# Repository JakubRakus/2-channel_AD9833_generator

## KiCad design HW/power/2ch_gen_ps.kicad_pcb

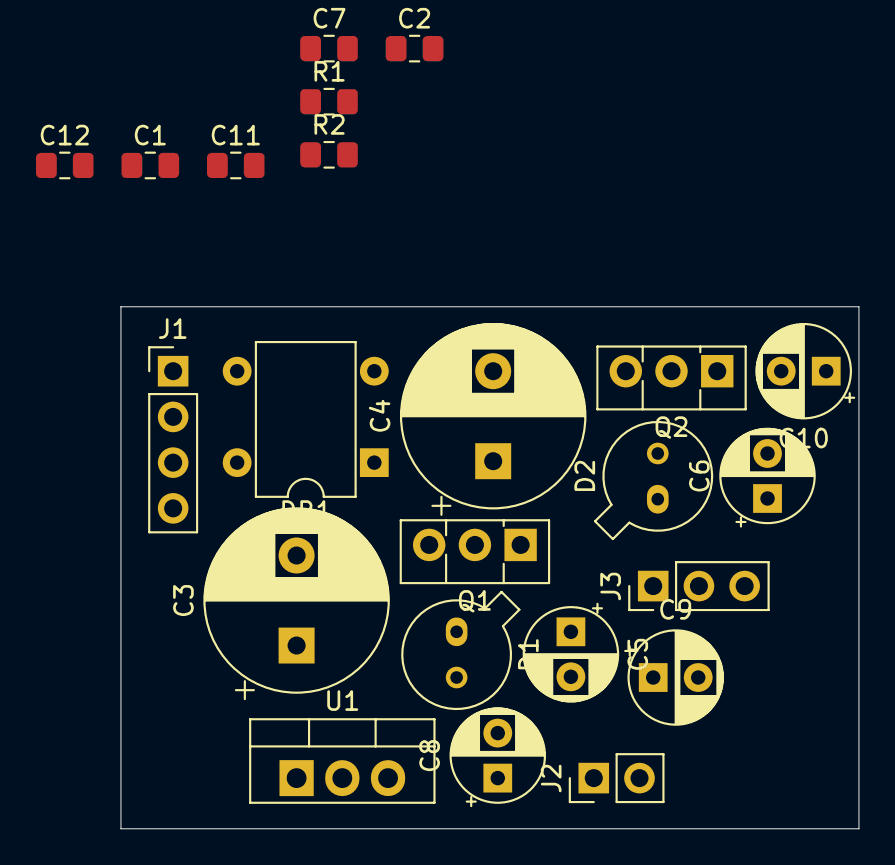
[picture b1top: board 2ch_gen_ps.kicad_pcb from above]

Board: 2 copper layers, 41.0 x 29.0 mm, 23 parts (0 on the bottom side), 10 nets, no tracks yet.

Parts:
C1, C2, C7, C11, C12: 100n; C_0805_2012Metric_Pad1.15x1.40mm_HandSolder
C3, C4: 2200u/16V; CP_Radial_D10.0mm_P5.00mm
C5, C6: 10u; CP_Radial_D5.0mm_P2.50mm
C8: 220u/6.3V; CP_Radial_D5.0mm_P2.50mm
C9, C10: 100u/10V; CP_Radial_D5.0mm_P2.50mm
D1, D2: 6V8; TO-18-2
DB1: DB106; Diode_Bridge_DIP-4_W7.62mm_P5.08mm
J1: Conn_01x04; PinHeader_1x04_P2.54mm_Vertical
J2: Conn_01x02; PinHeader_1x02_P2.54mm_Vertical
J3: Conn_01x03; PinHeader_1x03_P2.54mm_Vertical
Q1: BD139; TO-126-3_Vertical
Q2: BD140; TO-126-3_Vertical
R1, R2: 100R; R_0805_2012Metric_Pad1.15x1.40mm_HandSolder
U1: 7805; TO-220-3_Vertical

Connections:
+5V: C7.1, C8.1, J2.1, U1.3
/AC1: DB1.4, J1.4
/AC2*: DB1.3, J1.1
GND: C1.2, C2.1, C3.2, C4.1, C5.2, C6.1, C7.2, C8.2, C9.2, C10.1, C11.2, C12.1, D1.2, D2.1, J1.2, J1.3, J2.2, J3.2, U1.2
unnamed: C1.1, C3.1, DB1.1, Q1.2, R1.1, U1.1
unnamed: C2.2, C4.2, DB1.2, Q2.2, R2.2
unnamed: C5.1, D1.1, Q1.3, R1.2
unnamed: C6.2, D2.2, Q2.3, R2.1
VDDA: C9.1, C11.1, J3.1, Q1.1
VSSA: C10.2, C12.2, J3.3, Q2.1

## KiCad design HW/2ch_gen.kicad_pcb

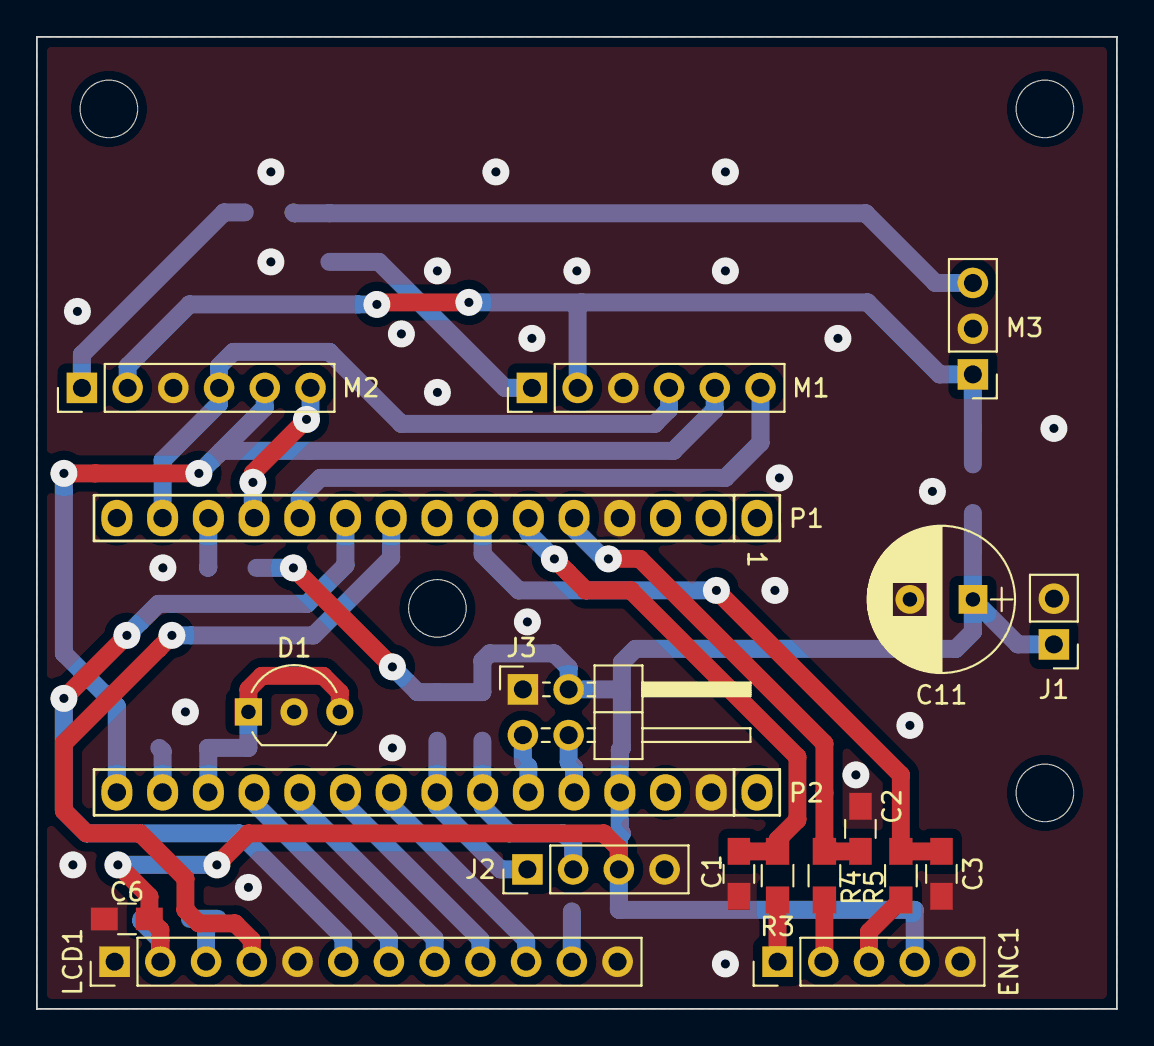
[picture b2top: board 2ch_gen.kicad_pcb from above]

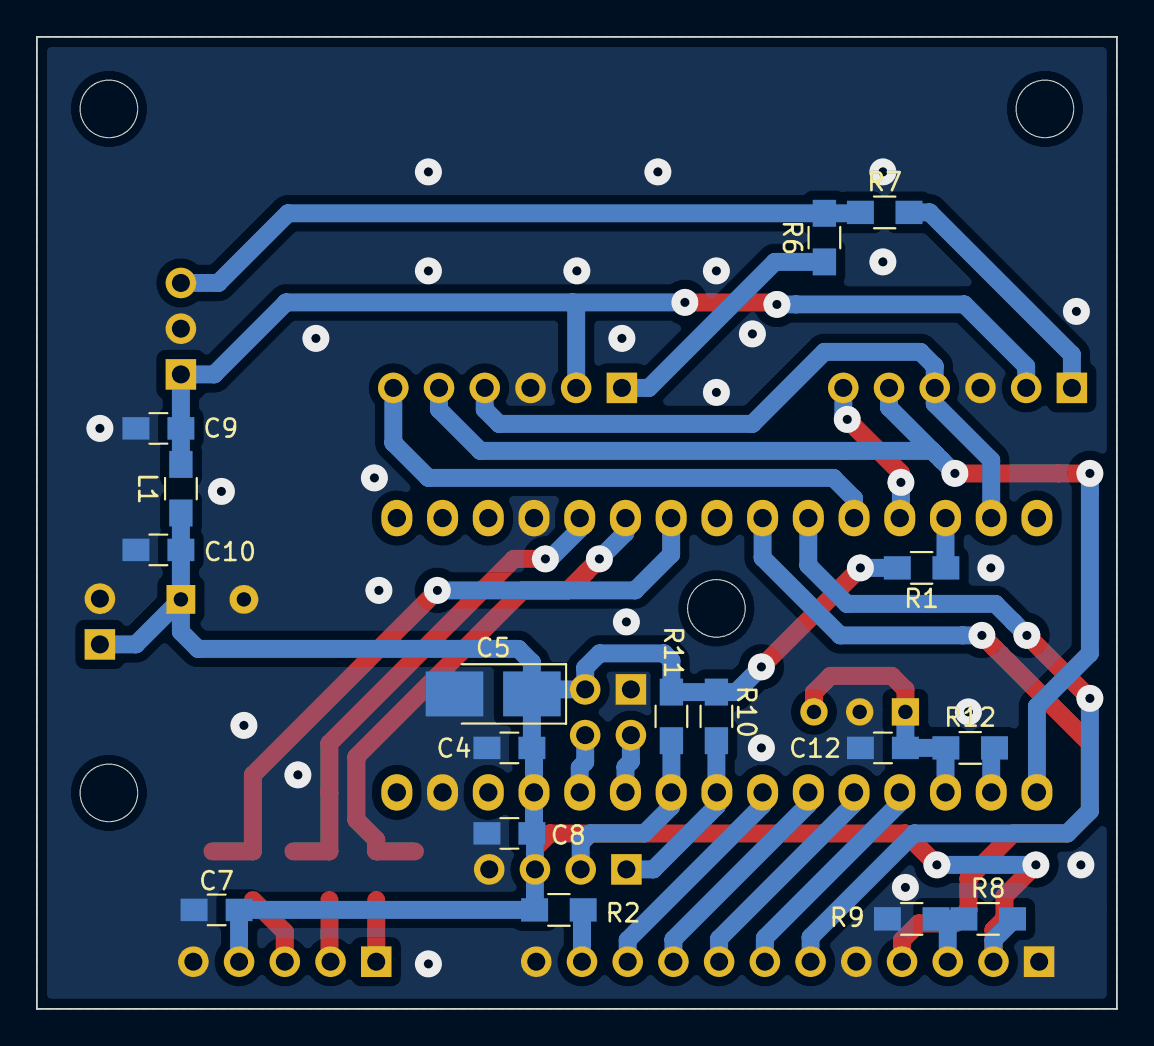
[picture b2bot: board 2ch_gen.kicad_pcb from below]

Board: 2 copper layers, 60.0 x 54.0 mm, 36 parts (17 on the bottom side), 20 nets.

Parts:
C1, C2, C3, C4, C6, C7, C8, C9, C10: 100n; C_0805_HandSoldering
C5: 10u; CP_Tantalum_Case-B_EIA-3528-21_Hand
C11: 1000u; CP_Radial_D8.0mm_P3.50mm
C12: 1u; C_0805_HandSoldering
D1: TL431; TO-92_Inline_Wide
ENC1: R_ENC; Pin_Header_Straight_1x05_Pitch2.54mm
J1: PWR; Pin_Header_Straight_1x02_Pitch2.54mm
J2: I2C_EXT; Pin_Header_Straight_1x04_Pitch2.54mm
J3: ANEXT; Pin_Header_Angled_2x02_Pitch2.54mm
L1: BLM21; R_0805_HandSoldering
LCD1: 2x16; Pin_Header_Straight_1x12_Pitch2.54mm
M1, M2: DDS_MOD; Pin_Header_Straight_1x06_Pitch2.54mm
M3: TCXO; Pin_Header_Straight_1x03_Pitch2.54mm
P1: Digital; Socket_Strip_Arduino_1x15
P2: Analog; Socket_Strip_Arduino_1x15
R1, R3, R4, R5: 10k; R_0805_HandSoldering
R2: 15; R_0805_HandSoldering
R6, R7: 0; R_0805_HandSoldering
R8: 51k; R_0805_HandSoldering
R9: 2k4; R_0805_HandSoldering
R10, R11: 2k1; R_0805_HandSoldering
R12: 470; R_0805_HandSoldering

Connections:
+5V: C4.2, C5.1, C6.2, C7.1, C8.1, C10.1, C11.1, ENC1.4, J1.1, J2.3, J3.2, L1.2, LCD1.2, P2.4, R1.2, R2.2, R8.2, R10.2, R11.2
+5VA: C9.1, L1.1, M1.2, M2.2, M3.1
/ENC_A: C1.1, R3.2
/ENC_B: C2.1, R4.2
/ENC_SW: C3.1, R5.2
/MCLK: M3.3, R6.1, R7.1
/MOSI: M1.4, M2.4
/Reset: P1.3, P2.3
/SCK: M1.5, M2.5
/SCL: J2.2, R11.1
/SDA: J2.1, R10.1
GND: C1.2, C2.2, C3.2, C4.1, C5.2, C6.1, C7.2, C8.2, C9.2, C10.2, C11.2, C12.2, D1.2, ENC1.5, J1.2, J2.4, J3.1, LCD1.1, LCD1.5, LCD1.12, M1.3, M2.3, M3.2, P1.4, P2.2, R9.1
unnamed: C12.1, D1.1, D1.3, R12.1
unnamed: ENC1.1, R3.1
unnamed: ENC1.2, R4.1
unnamed: ENC1.3, R5.1
unnamed: LCD1.3, R8.1, R9.2
unnamed: LCD1.11, R2.1
unnamed: M1.1, R6.2
unnamed: M2.1, R7.2

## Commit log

2018-06-09 inital commit
2018-06-12 custom characters write to LCD CGRAM
2018-06-13 custom LCD characters - channel 1, channel 2
2018-06-14 LCD - wave-shape icons changed to abbreviations
2018-06-15 transition between main screen and channel menu
2018-06-18 changes in FSM state transitions
2018-06-18 LCD custom characters - channel 1, channel 2 icons
2018-06-26 additional options screen - phase edit
2018-06-26 fix: calculating AD9833 phase register value
2019-02-09 changes in signal phase control (range -180 to 180 degrees instead of 0 to 360) and minor changes in gitignore for HW
2019-02-11 added power supply basic schematic, changed structure of HW directory
2019-02-18 initial placement of THT elements on top side of power supply PCB
